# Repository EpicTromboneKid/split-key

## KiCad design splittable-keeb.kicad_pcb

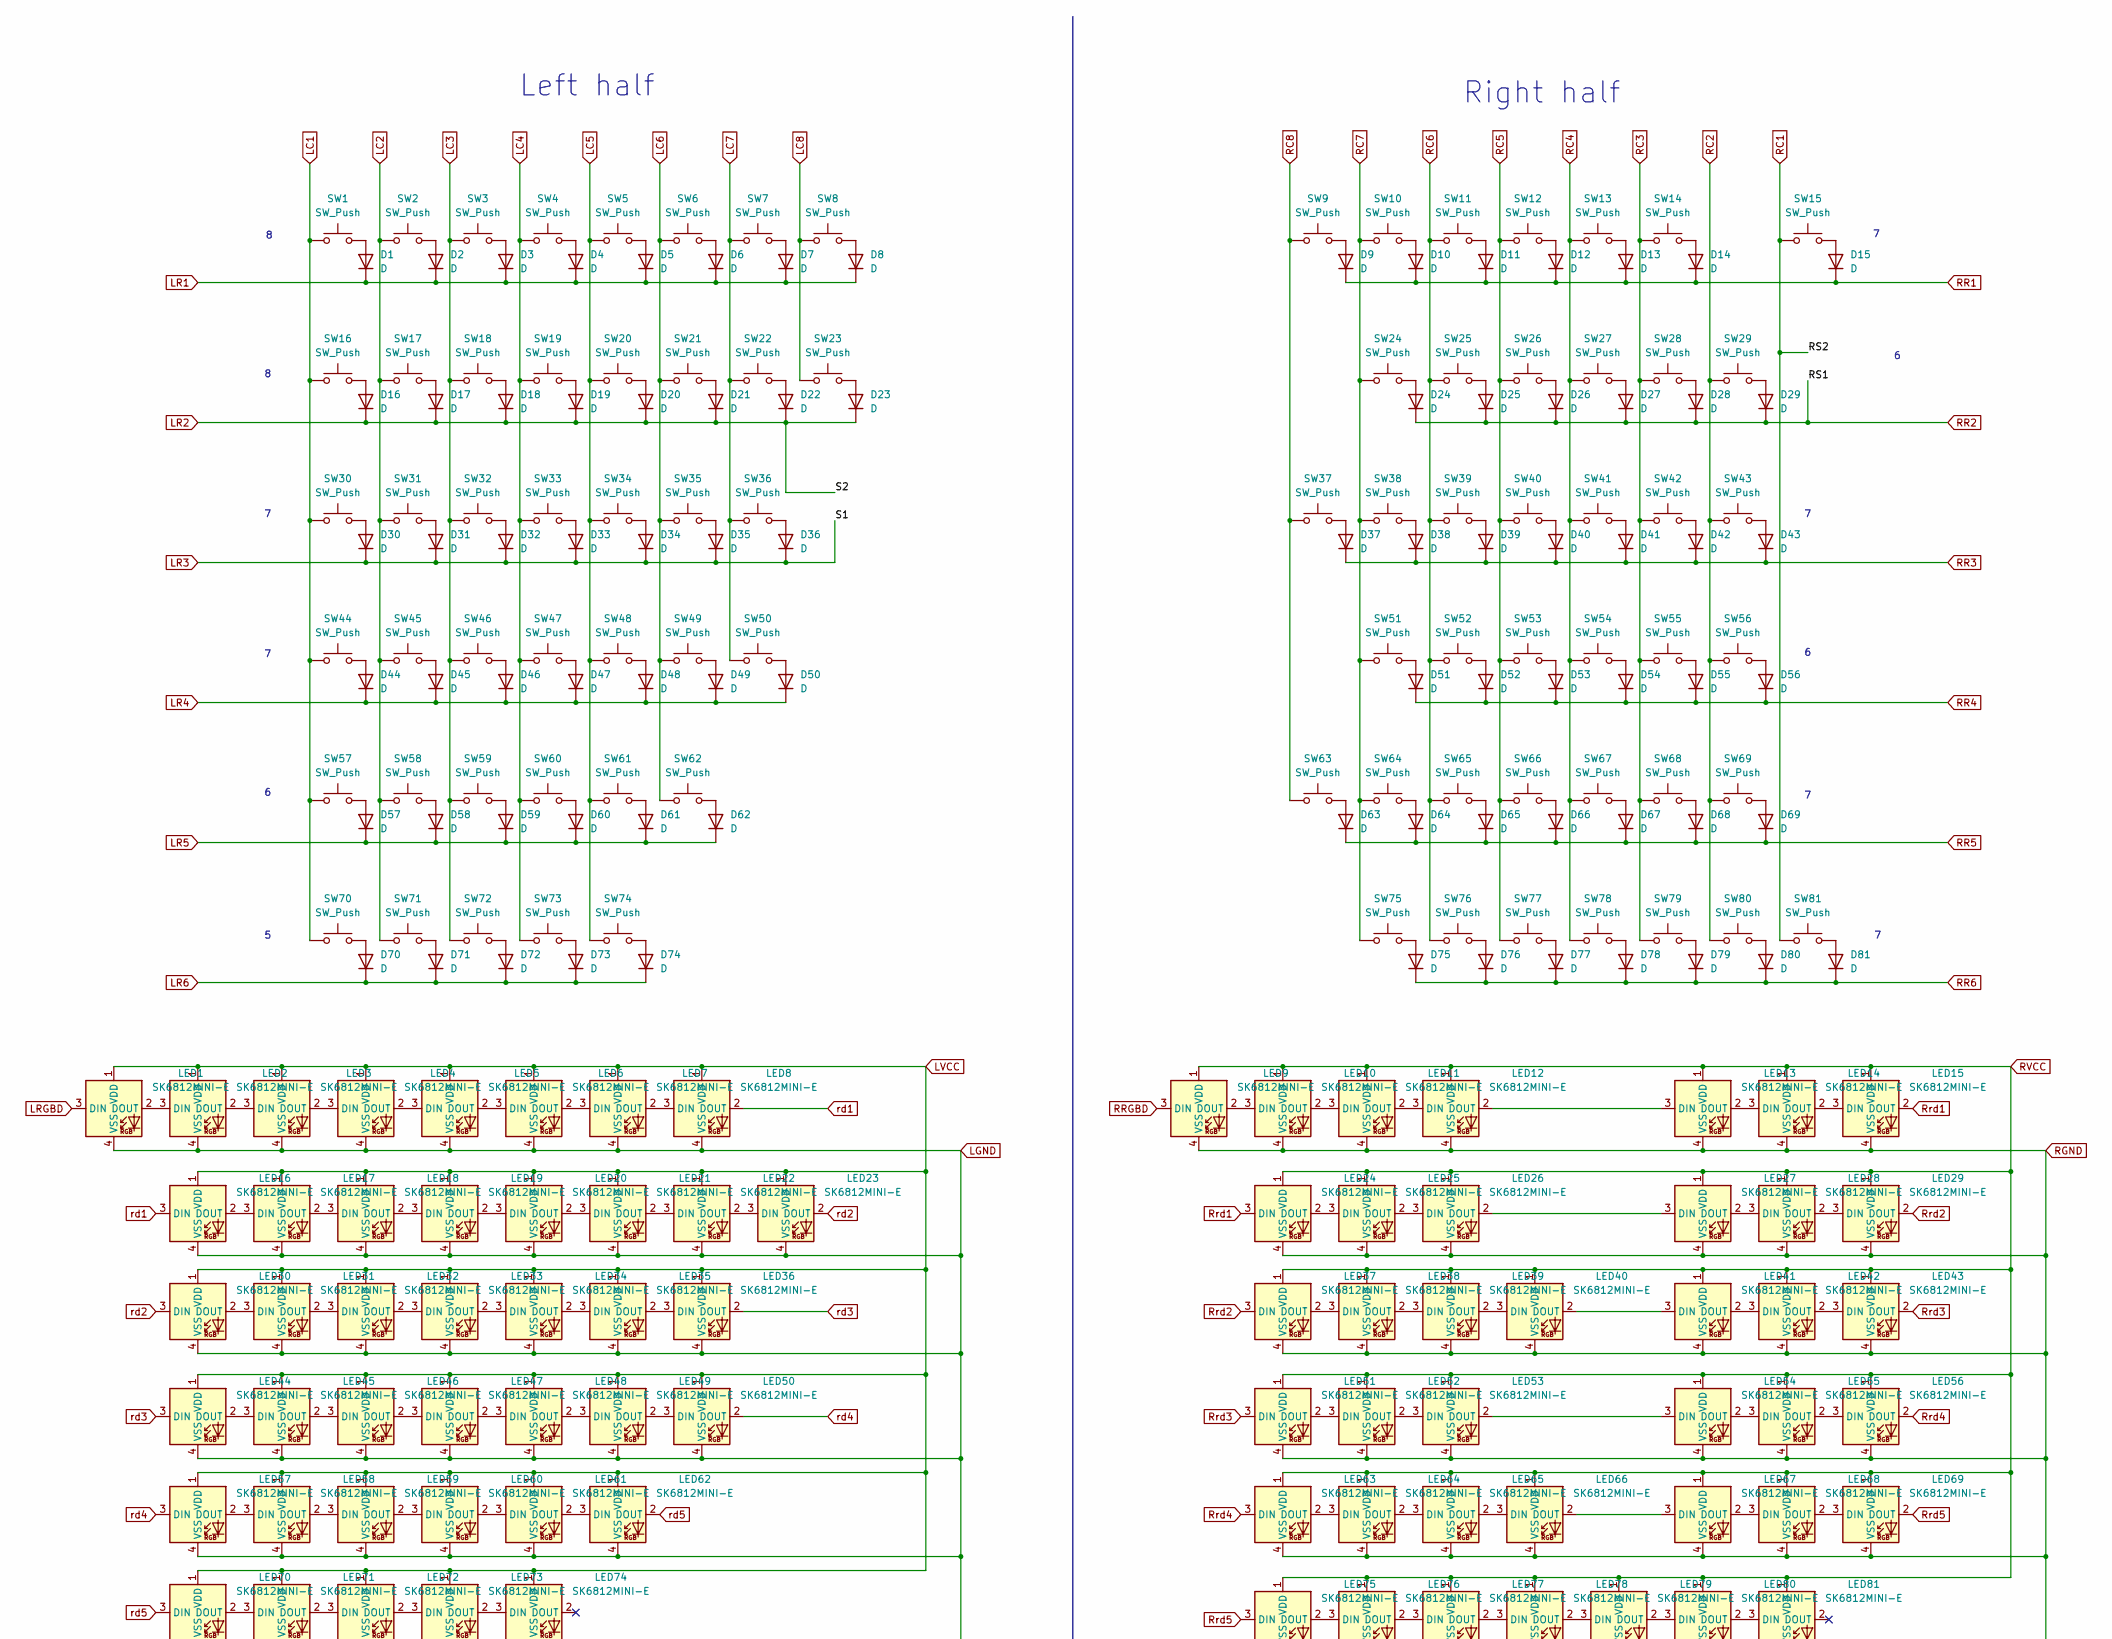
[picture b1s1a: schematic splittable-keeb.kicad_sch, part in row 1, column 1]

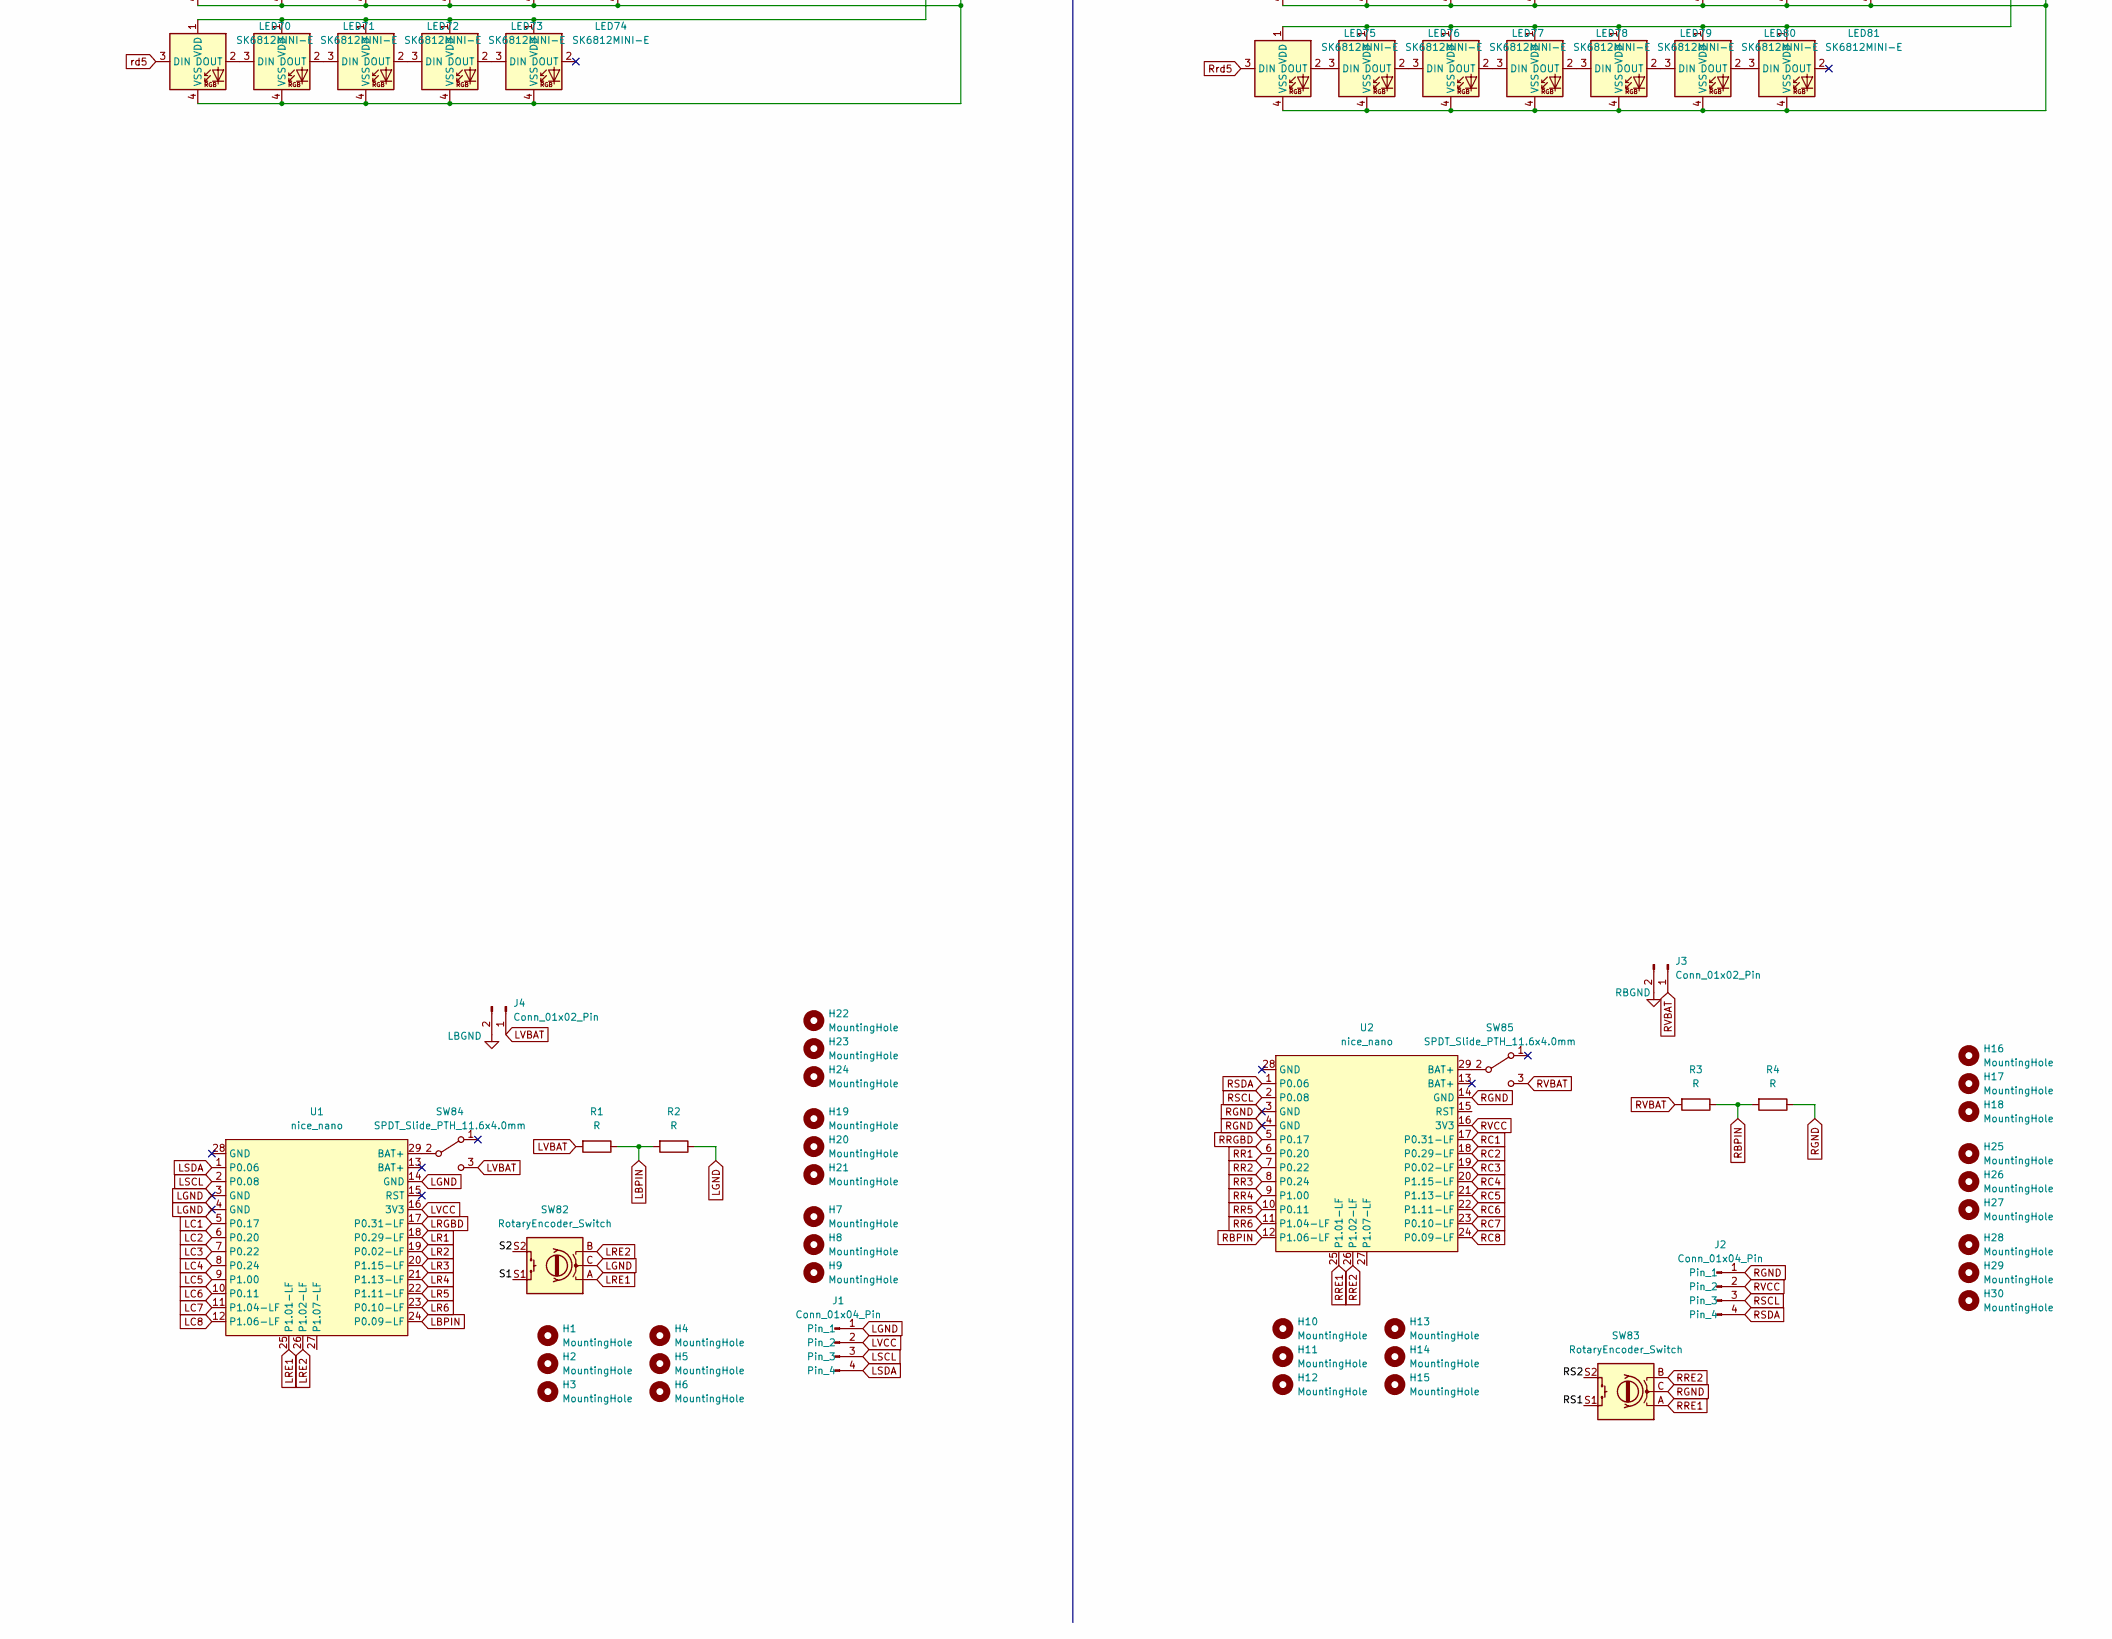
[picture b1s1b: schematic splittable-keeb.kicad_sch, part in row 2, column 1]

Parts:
D1, D2, D3, D4, D5, D6, D7, D8, D9, D10, D11, D12, D13, D14, D15, D16, D17, D18, D19, D20, D21, D22, D23, D24, D25, D26, D27, D28, D29, D30, D31, D32, D33, D34, D35, D36, D37, D38, D39, D40, D41, D42, D43, D44, D45, D46, D47, D48, D49, D50, D51, D52, D53, D54, D55, D56, D57, D58, D59, D60, D61, D62, D63, D64, D65, D66, D67, D68, D69, D70, D71, D72, D73, D74, D75, D76, D77, D78, D79, D80, D81: D; D_SOD-123
H1, H2, H3, H4, H5, H6, H10, H11, H12, H13, H14, H15: MountingHole; MountingHole_3.2mm_M3
H7, H8, H9, H16, H17, H18, H19, H20, H21, H22, H23, H24, H25, H26, H27, H28, H29, H30: MountingHole; mousebites_1mm
J1, J2: Conn_01x04_Pin; SSD1306-0.91-OLED-4pin-128x32
J3, J4: Conn_01x02_Pin; JST_PH_B2B-PH-K_1x02_P2.00mm_Vertical
LED1, LED2, LED3, LED4, LED5, LED6, LED7, LED8, LED9, LED10, LED11, LED12, LED13, LED14, LED15, LED16, LED17, LED18, LED19, LED20, LED21, LED22, LED23, LED24, LED25, LED26, LED27, LED28, LED29, LED30, LED31, LED32, LED33, LED34, LED35, LED36, LED37, LED38, LED39, LED40, LED41, LED42, LED43, LED44, LED45, LED46, LED47, LED48, LED49, LED50, LED51, LED52, LED53, LED54, LED55, LED56, LED57, LED58, LED59, LED60, LED61, LED62, LED63, LED64, LED65, LED66, LED67, LED68, LED69, LED70, LED71, LED72, LED73, LED74, LED75, LED76, LED77, LED78, LED79, LED80, LED81: SK6812MINI-E; LED_6028R
R1, R2, R3, R4: R; R_0805_2012Metric_Pad1.20x1.40mm_HandSolder
SW1, SW2, SW3, SW4, SW5, SW6, SW7, SW8, SW9, SW10, SW11, SW12, SW13, SW14, SW15, SW16, SW17, SW18, SW19, SW20, SW21, SW22, SW23, SW24, SW25, SW26, SW27, SW28, SW31, SW32, SW33, SW34, SW35, SW36, SW37, SW38, SW39, SW40, SW41, SW42, SW45, SW46, SW47, SW48, SW49, SW50, SW51, SW52, SW53, SW54, SW55, SW58, SW59, SW60, SW61, SW62, SW63, SW64, SW65, SW66, SW67, SW69, SW79, SW80, SW81: SW_Push; SW_Cherry_MX_1.00u_PCB
SW29: SW_Push; SW_Cherry_MX_2.00u_PCB
SW30, SW43: SW_Push; SW_Cherry_MX_1.50u_PCB
SW44, SW68: SW_Push; SW_Cherry_MX_1.75u_PCB
SW56, SW57: SW_Push; SW_Cherry_MX_2.25u_PCB
SW70, SW71, SW72, SW73, SW76, SW77, SW78: SW_Push; SW_Cherry_MX_1.25u_PCB
SW74, SW75: SW_Push; SW_Cherry_MX_2.75u_PCB
SW82, SW83: RotaryEncoder_Switch; ROT_Alps_EC11E-Switch
SW84, SW85: SPDT_Slide_PTH_11.6x4.0mm; Slide_SPDT_PTH_11.6x4.0mm
U1, U2: nice_nano; SuperMini NRF52840

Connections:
LBGND: J4.2
LBPIN: R1.1, R2.2, U1.24 (P0.09-LF)
LC1: SW1.1, SW16.1, SW30.1, SW44.1, SW57.1, SW70.1, U1.5 (P0.17)
LC2: SW2.1, SW17.1, SW31.1, SW45.1, SW58.1, SW71.1, U1.6 (P0.20)
LC3: SW3.1, SW18.1, SW32.1, SW46.1, SW59.1, SW72.1, U1.7 (P0.22)
LC4: SW4.1, SW19.1, SW33.1, SW47.1, SW60.1, SW73.1, U1.8 (P0.24)
LC5: SW5.1, SW20.1, SW34.1, SW48.1, SW61.1, SW74.1, U1.9 (P1.00)
LC6: SW6.1, SW21.1, SW35.1, SW49.1, SW62.1, U1.10 (P0.11)
LC7: SW7.1, SW22.1, SW36.1, SW50.1, U1.11 (P1.04-LF)
LC8: SW8.1, SW23.1, U1.12 (P1.06-LF)
LGND: J1.1, LED1.4 (VSS), LED2.4 (VSS), LED3.4 (VSS), LED4.4 (VSS), LED5.4 (VSS), LED6.4 (VSS), LED7.4 (VSS), LED8.4 (VSS), LED16.4 (VSS), LED17.4 (VSS), LED18.4 (VSS), LED19.4 (VSS), LED20.4 (VSS), LED21.4 (VSS), LED22.4 (VSS), LED23.4 (VSS), LED30.4 (VSS), LED31.4 (VSS), LED32.4 (VSS), LED33.4 (VSS), LED34.4 (VSS), LED35.4 (VSS), LED36.4 (VSS), LED44.4 (VSS), LED45.4 (VSS), LED46.4 (VSS), LED47.4 (VSS), LED48.4 (VSS), LED49.4 (VSS), LED50.4 (VSS), LED57.4 (VSS), LED58.4 (VSS), LED59.4 (VSS), LED60.4 (VSS), LED61.4 (VSS), LED62.4 (VSS), LED70.4 (VSS), LED71.4 (VSS), LED72.4 (VSS), LED73.4 (VSS), LED74.4 (VSS), R2.1, SW82.C, U1.3 (GND), U1.4 (GND), U1.14 (GND)
LR1: D1.1 (K), D2.1 (K), D3.1 (K), D4.1 (K), D5.1 (K), D6.1 (K), D7.1 (K), D8.1 (K), U1.18 (P0.29-LF)
LR2: D16.1 (K), D17.1 (K), D18.1 (K), D19.1 (K), D20.1 (K), D21.1 (K), D22.1 (K), D23.1 (K), SW82.S2, U1.19 (P0.02-LF)
LR3: D30.1 (K), D31.1 (K), D32.1 (K), D33.1 (K), D34.1 (K), D35.1 (K), D36.1 (K), SW82.S1, U1.20 (P1.15-LF)
LR4: D44.1 (K), D45.1 (K), D46.1 (K), D47.1 (K), D48.1 (K), D49.1 (K), D50.1 (K), U1.21 (P1.13-LF)
LR5: D57.1 (K), D58.1 (K), D59.1 (K), D60.1 (K), D61.1 (K), D62.1 (K), U1.22 (P1.11-LF)
LR6: D70.1 (K), D71.1 (K), D72.1 (K), D73.1 (K), D74.1 (K), U1.23 (P0.10-LF)
LRE1: SW82.A, U1.25 (P1.01-LF)
LRE2: SW82.B, U1.26 (P1.02-LF)
LRGBD: LED1.3 (DIN), U1.17 (P0.31-LF)
LSCL: J1.3, U1.2 (P0.08)
LSDA: J1.4, U1.1 (P0.06)
LVBAT: J4.1, R1.2, SW84.3 (C)
LVCC: J1.2, LED1.1 (VDD), LED2.1 (VDD), LED3.1 (VDD), LED4.1 (VDD), LED5.1 (VDD), LED6.1 (VDD), LED7.1 (VDD), LED8.1 (VDD), LED16.1 (VDD), LED17.1 (VDD), LED18.1 (VDD), LED19.1 (VDD), LED20.1 (VDD), LED21.1 (VDD), LED22.1 (VDD), LED23.1 (VDD), LED30.1 (VDD), LED31.1 (VDD), LED32.1 (VDD), LED33.1 (VDD), LED34.1 (VDD), LED35.1 (VDD), LED36.1 (VDD), LED44.1 (VDD), LED45.1 (VDD), LED46.1 (VDD), LED47.1 (VDD), LED48.1 (VDD), LED49.1 (VDD), LED50.1 (VDD), LED57.1 (VDD), LED58.1 (VDD), LED59.1 (VDD), LED60.1 (VDD), LED61.1 (VDD), LED62.1 (VDD), LED70.1 (VDD), LED71.1 (VDD), LED72.1 (VDD), LED73.1 (VDD), LED74.1 (VDD), U1.16 (3V3)
unnamed: D1.2 (A), SW1.2
unnamed: D2.2 (A), SW2.2
unnamed: D3.2 (A), SW3.2
unnamed: D4.2 (A), SW4.2
unnamed: D5.2 (A), SW5.2
unnamed: D6.2 (A), SW6.2
unnamed: D7.2 (A), SW7.2
unnamed: D8.2 (A), SW8.2
unnamed: D9.2 (A), SW9.2
unnamed: D10.2 (A), SW10.2
unnamed: D11.2 (A), SW11.2
unnamed: D12.2 (A), SW12.2
unnamed: D13.2 (A), SW13.2
unnamed: D14.2 (A), SW14.2
unnamed: D15.2 (A), SW15.2
unnamed: D16.2 (A), SW16.2
unnamed: D17.2 (A), SW17.2
unnamed: D18.2 (A), SW18.2
unnamed: D19.2 (A), SW19.2
unnamed: D20.2 (A), SW20.2
unnamed: D21.2 (A), SW21.2
unnamed: D22.2 (A), SW22.2
unnamed: D23.2 (A), SW23.2
unnamed: D24.2 (A), SW24.2
unnamed: D25.2 (A), SW25.2
unnamed: D26.2 (A), SW26.2
unnamed: D27.2 (A), SW27.2
unnamed: D28.2 (A), SW28.2
unnamed: D29.2 (A), SW29.2
unnamed: D30.2 (A), SW30.2
unnamed: D31.2 (A), SW31.2
unnamed: D32.2 (A), SW32.2
unnamed: D33.2 (A), SW33.2
unnamed: D34.2 (A), SW34.2
unnamed: D35.2 (A), SW35.2
unnamed: D36.2 (A), SW36.2
unnamed: D37.2 (A), SW37.2
unnamed: D38.2 (A), SW38.2
unnamed: D39.2 (A), SW39.2
unnamed: D40.2 (A), SW40.2
unnamed: D41.2 (A), SW41.2
unnamed: D42.2 (A), SW42.2
unnamed: D43.2 (A), SW43.2
unnamed: D44.2 (A), SW44.2
unnamed: D45.2 (A), SW45.2
unnamed: D46.2 (A), SW46.2
unnamed: D47.2 (A), SW47.2
unnamed: D48.2 (A), SW48.2
unnamed: D49.2 (A), SW49.2
unnamed: D50.2 (A), SW50.2
unnamed: D51.2 (A), SW51.2
unnamed: D52.2 (A), SW52.2
unnamed: D53.2 (A), SW53.2
unnamed: D54.2 (A), SW54.2
unnamed: D55.2 (A), SW55.2
unnamed: D56.2 (A), SW56.2
unnamed: D57.2 (A), SW57.2
unnamed: D58.2 (A), SW58.2
unnamed: D59.2 (A), SW59.2
unnamed: D60.2 (A), SW60.2
unnamed: D61.2 (A), SW61.2
unnamed: D62.2 (A), SW62.2
unnamed: D63.2 (A), SW63.2
unnamed: D64.2 (A), SW64.2
unnamed: D65.2 (A), SW65.2
unnamed: D66.2 (A), SW66.2
unnamed: D67.2 (A), SW67.2
unnamed: D68.2 (A), SW68.2
unnamed: D69.2 (A), SW69.2
unnamed: D70.2 (A), SW70.2
unnamed: D71.2 (A), SW71.2
unnamed: D72.2 (A), SW72.2
unnamed: D73.2 (A), SW73.2
unnamed: D74.2 (A), SW74.2
unnamed: D75.2 (A), SW75.2
unnamed: D76.2 (A), SW76.2
unnamed: D77.2 (A), SW77.2
unnamed: D78.2 (A), SW78.2
unnamed: D79.2 (A), SW79.2
unnamed: D80.2 (A), SW80.2
unnamed: D81.2 (A), SW81.2
unnamed: LED1.2 (DOUT), LED2.3 (DIN)
unnamed: LED2.2 (DOUT), LED3.3 (DIN)
unnamed: LED3.2 (DOUT), LED4.3 (DIN)
unnamed: LED4.2 (DOUT), LED5.3 (DIN)
unnamed: LED5.2 (DOUT), LED6.3 (DIN)
unnamed: LED6.2 (DOUT), LED7.3 (DIN)
unnamed: LED7.2 (DOUT), LED8.3 (DIN)
unnamed: LED9.2 (DOUT), LED10.3 (DIN)
unnamed: LED10.2 (DOUT), LED11.3 (DIN)
unnamed: LED11.2 (DOUT), LED12.3 (DIN)
unnamed: LED12.2 (DOUT), LED13.3 (DIN)
unnamed: LED13.2 (DOUT), LED14.3 (DIN)
unnamed: LED14.2 (DOUT), LED15.3 (DIN)
unnamed: LED16.2 (DOUT), LED17.3 (DIN)
unnamed: LED17.2 (DOUT), LED18.3 (DIN)
unnamed: LED18.2 (DOUT), LED19.3 (DIN)
unnamed: LED19.2 (DOUT), LED20.3 (DIN)
unnamed: LED20.2 (DOUT), LED21.3 (DIN)
unnamed: LED21.2 (DOUT), LED22.3 (DIN)
unnamed: LED22.2 (DOUT), LED23.3 (DIN)
unnamed: LED24.2 (DOUT), LED25.3 (DIN)
unnamed: LED25.2 (DOUT), LED26.3 (DIN)
unnamed: LED26.2 (DOUT), LED27.3 (DIN)
unnamed: LED27.2 (DOUT), LED28.3 (DIN)
unnamed: LED28.2 (DOUT), LED29.3 (DIN)
unnamed: LED30.2 (DOUT), LED31.3 (DIN)
unnamed: LED31.2 (DOUT), LED32.3 (DIN)
unnamed: LED32.2 (DOUT), LED33.3 (DIN)
unnamed: LED33.2 (DOUT), LED34.3 (DIN)
unnamed: LED34.2 (DOUT), LED35.3 (DIN)
unnamed: LED35.2 (DOUT), LED36.3 (DIN)
unnamed: LED37.2 (DOUT), LED38.3 (DIN)
unnamed: LED38.2 (DOUT), LED39.3 (DIN)
unnamed: LED39.2 (DOUT), LED40.3 (DIN)
unnamed: LED40.2 (DOUT), LED41.3 (DIN)
unnamed: LED41.2 (DOUT), LED42.3 (DIN)
unnamed: LED42.2 (DOUT), LED43.3 (DIN)
unnamed: LED44.2 (DOUT), LED45.3 (DIN)
unnamed: LED45.2 (DOUT), LED46.3 (DIN)
unnamed: LED46.2 (DOUT), LED47.3 (DIN)
unnamed: LED47.2 (DOUT), LED48.3 (DIN)
unnamed: LED48.2 (DOUT), LED49.3 (DIN)
unnamed: LED49.2 (DOUT), LED50.3 (DIN)
unnamed: LED51.2 (DOUT), LED52.3 (DIN)
unnamed: LED52.2 (DOUT), LED53.3 (DIN)
unnamed: LED53.2 (DOUT), LED54.3 (DIN)
unnamed: LED54.2 (DOUT), LED55.3 (DIN)
unnamed: LED55.2 (DOUT), LED56.3 (DIN)
unnamed: LED57.2 (DOUT), LED58.3 (DIN)
unnamed: LED58.2 (DOUT), LED59.3 (DIN)
unnamed: LED59.2 (DOUT), LED60.3 (DIN)
unnamed: LED60.2 (DOUT), LED61.3 (DIN)
unnamed: LED61.2 (DOUT), LED62.3 (DIN)
unnamed: LED63.2 (DOUT), LED64.3 (DIN)
unnamed: LED64.2 (DOUT), LED65.3 (DIN)
unnamed: LED65.2 (DOUT), LED66.3 (DIN)
unnamed: LED66.2 (DOUT), LED67.3 (DIN)
unnamed: LED67.2 (DOUT), LED68.3 (DIN)
unnamed: LED68.2 (DOUT), LED69.3 (DIN)
unnamed: LED70.2 (DOUT), LED71.3 (DIN)
unnamed: LED71.2 (DOUT), LED72.3 (DIN)
unnamed: LED72.2 (DOUT), LED73.3 (DIN)
unnamed: LED73.2 (DOUT), LED74.3 (DIN)
unnamed: LED75.2 (DOUT), LED76.3 (DIN)
unnamed: LED76.2 (DOUT), LED77.3 (DIN)
unnamed: LED77.2 (DOUT), LED78.3 (DIN)
unnamed: LED78.2 (DOUT), LED79.3 (DIN)
unnamed: LED79.2 (DOUT), LED80.3 (DIN)
unnamed: LED80.2 (DOUT), LED81.3 (DIN)
unnamed: SW84.2 (B), U1.29 (BAT+)
unnamed: SW85.2 (B), U2.29 (BAT+)
RBGND: J3.2
RBPIN: R3.1, R4.2, U2.12 (P1.06-LF)
RC1: SW15.1, SW81.1, SW83.S2, U2.17 (P0.31-LF)
RC2: SW29.1, SW43.1, SW56.1, SW69.1, SW80.1, U2.18 (P0.29-LF)
RC3: SW14.1, SW28.1, SW42.1, SW55.1, SW68.1, SW79.1, U2.19 (P0.02-LF)
RC4: SW13.1, SW27.1, SW41.1, SW54.1, SW67.1, SW78.1, U2.20 (P1.15-LF)
RC5: SW12.1, SW26.1, SW40.1, SW53.1, SW66.1, SW77.1, U2.21 (P1.13-LF)
RC6: SW11.1, SW25.1, SW39.1, SW52.1, SW65.1, SW76.1, U2.22 (P1.11-LF)
RC7: SW10.1, SW24.1, SW38.1, SW51.1, SW64.1, SW75.1, U2.23 (P0.10-LF)
RC8: SW9.1, SW37.1, SW63.1, U2.24 (P0.09-LF)
RGND: J2.1, LED9.4 (VSS), LED10.4 (VSS), LED11.4 (VSS), LED12.4 (VSS), LED13.4 (VSS), LED14.4 (VSS), LED15.4 (VSS), LED24.4 (VSS), LED25.4 (VSS), LED26.4 (VSS), LED27.4 (VSS), LED28.4 (VSS), LED29.4 (VSS), LED37.4 (VSS), LED38.4 (VSS), LED39.4 (VSS), LED40.4 (VSS), LED41.4 (VSS), LED42.4 (VSS), LED43.4 (VSS), LED51.4 (VSS), LED52.4 (VSS), LED53.4 (VSS), LED54.4 (VSS), LED55.4 (VSS), LED56.4 (VSS), LED63.4 (VSS), LED64.4 (VSS), LED65.4 (VSS), LED66.4 (VSS), LED67.4 (VSS), LED68.4 (VSS), LED69.4 (VSS), LED75.4 (VSS), LED76.4 (VSS), LED77.4 (VSS), LED78.4 (VSS), LED79.4 (VSS), LED80.4 (VSS), LED81.4 (VSS), R4.1, SW83.C, U2.3 (GND), U2.4 (GND), U2.14 (GND)
RR1: D9.1 (K), D10.1 (K), D11.1 (K), D12.1 (K), D13.1 (K), D14.1 (K), D15.1 (K), U2.6 (P0.20)
RR2: D24.1 (K), D25.1 (K), D26.1 (K), D27.1 (K), D28.1 (K), D29.1 (K), SW83.S1, U2.7 (P0.22)
RR3: D37.1 (K), D38.1 (K), D39.1 (K), D40.1 (K), D41.1 (K), D42.1 (K), D43.1 (K), U2.8 (P0.24)
RR4: D51.1 (K), D52.1 (K), D53.1 (K), D54.1 (K), D55.1 (K), D56.1 (K), U2.9 (P1.00)
RR5: D63.1 (K), D64.1 (K), D65.1 (K), D66.1 (K), D67.1 (K), D68.1 (K), D69.1 (K), U2.10 (P0.11)
RR6: D75.1 (K), D76.1 (K), D77.1 (K), D78.1 (K), D79.1 (K), D80.1 (K), D81.1 (K), U2.11 (P1.04-LF)
RRE1: SW83.A, U2.25 (P1.01-LF)
RRE2: SW83.B, U2.26 (P1.02-LF)
RRGBD: LED9.3 (DIN), U2.5 (P0.17)
RSCL: J2.3, U2.2 (P0.08)
RSDA: J2.4, U2.1 (P0.06)
RVBAT: J3.1, R3.2, SW85.3 (C)
RVCC: J2.2, LED9.1 (VDD), LED10.1 (VDD), LED11.1 (VDD), LED12.1 (VDD), LED13.1 (VDD), LED14.1 (VDD), LED15.1 (VDD), LED24.1 (VDD), LED25.1 (VDD), LED26.1 (VDD), LED27.1 (VDD), LED28.1 (VDD), LED29.1 (VDD), LED37.1 (VDD), LED38.1 (VDD), LED39.1 (VDD), LED40.1 (VDD), LED41.1 (VDD), LED42.1 (VDD), LED43.1 (VDD), LED51.1 (VDD), LED52.1 (VDD), LED53.1 (VDD), LED54.1 (VDD), LED55.1 (VDD), LED56.1 (VDD), LED63.1 (VDD), LED64.1 (VDD), LED65.1 (VDD), LED66.1 (VDD), LED67.1 (VDD), LED68.1 (VDD), LED69.1 (VDD), LED75.1 (VDD), LED76.1 (VDD), LED77.1 (VDD), LED78.1 (VDD), LED79.1 (VDD), LED80.1 (VDD), LED81.1 (VDD), U2.16 (3V3)
Rrd1: LED15.2 (DOUT), LED24.3 (DIN)
Rrd2: LED29.2 (DOUT), LED37.3 (DIN)
Rrd3: LED43.2 (DOUT), LED51.3 (DIN)
Rrd4: LED56.2 (DOUT), LED63.3 (DIN)
Rrd5: LED69.2 (DOUT), LED75.3 (DIN)
rd1: LED8.2 (DOUT), LED16.3 (DIN)
rd2: LED23.2 (DOUT), LED30.3 (DIN)
rd3: LED36.2 (DOUT), LED44.3 (DIN)
rd4: LED50.2 (DOUT), LED57.3 (DIN)
rd5: LED62.2 (DOUT), LED70.3 (DIN)

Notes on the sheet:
Left half
Right half

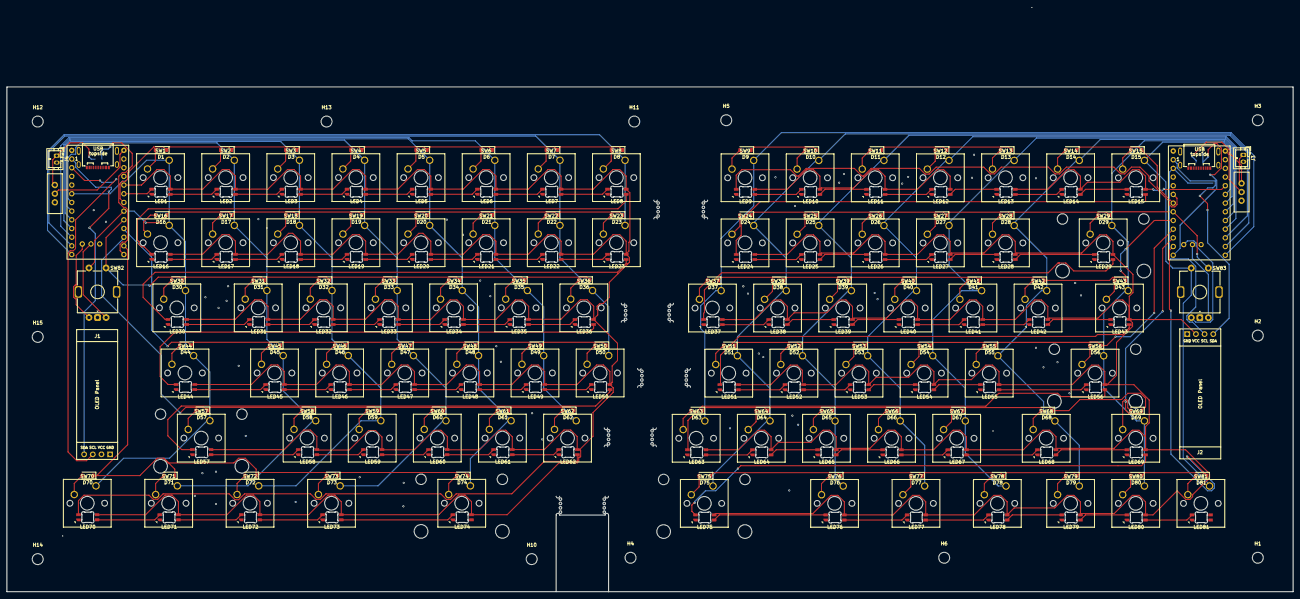
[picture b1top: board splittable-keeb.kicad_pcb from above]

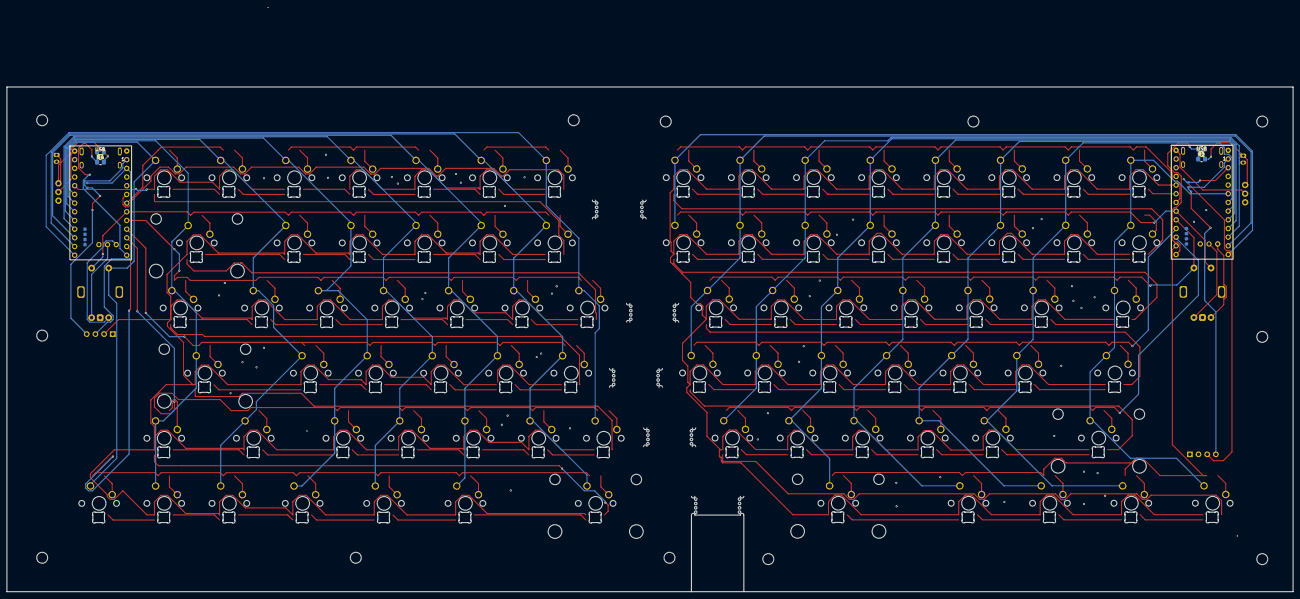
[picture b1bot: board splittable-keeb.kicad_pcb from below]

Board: 2 copper layers, 375.9 x 170.7 mm, 279 parts (4 on the bottom side), 208 nets.

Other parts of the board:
H9#2, H9#3, H9#4, H23#2, H23#3, H23#4, H25#2: MountingHole; mousebites_1mm

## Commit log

2026-06-23 pushing pcb because apparently i didnt push it until now
